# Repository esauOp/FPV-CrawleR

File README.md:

This is a little toy hack. I add an electronics H bridge for speed control and RC compatibility (PWM read).

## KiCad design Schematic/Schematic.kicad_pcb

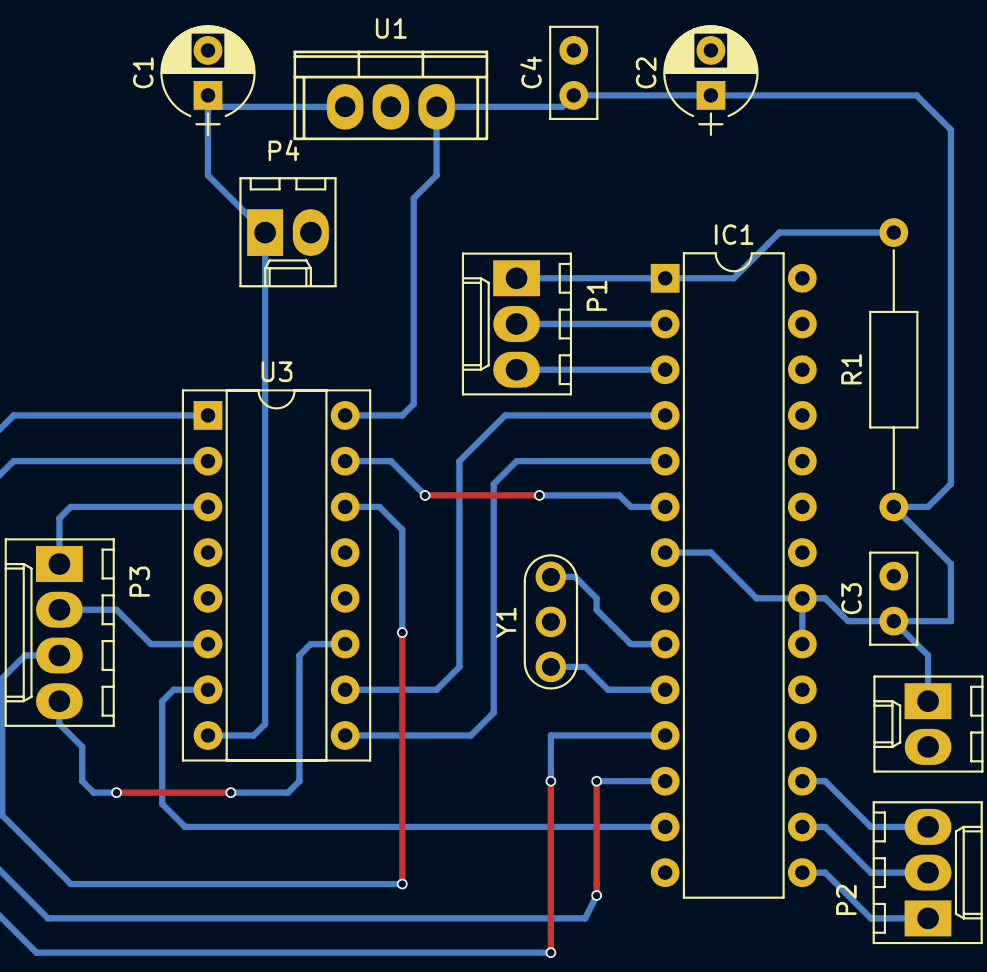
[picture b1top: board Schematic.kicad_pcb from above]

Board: 2 copper layers, 14 parts (0 on the bottom side), 21 nets.

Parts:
C1, C2: 10uF; CP_Radial_D5.0mm_P2.50mm
C3, C4: 100nF; C_Disc_D5.0mm_W2.5mm_P2.50mm
IC1: ATMEGA328-P; DIP-28_W7.62mm
P1: Arduino Programmer; Molex_KK-6410-03_03x2.54mm_Straight
P2: X8R; Molex_KK-6410-03_03x2.54mm_Straight
P3: Motors; Molex_KK-6410-04_04x2.54mm_Straight
P4: Motors Voltage; Molex_KK-6410-02_02x2.54mm_Straight
P5: Rx PS; Molex_KK-6410-02_02x2.54mm_Straight
R1: 10k; R_Axial_DIN0207_L6.3mm_D2.5mm_P15.24mm_Horizontal
U1: LM7805; TO-220
U3: SN754410; DIP-16_W7.62mm_Socket
Y1: Resonator; Resonator-3pin_w7.0mm_h2.5mm

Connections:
+5V: C2.1, C3.1, C4.1, IC1.7, IC1.20, IC1.21, P5.1, R1.1, U1.3, U3.16
+9V: C1.1, P4.1, U1.1, U3.8
GND: C1.2, C2.2, C3.2, C4.2, IC1.8, IC1.22, P4.2, P5.2, U1.2, U3.4, U3.5, U3.12, U3.13, Y1.2
RTS: IC1.1, P1.1, R1.2
Rx: IC1.2, P1.2
Tx: IC1.3, P1.3
ch1: IC1.17, P2.3
ch2: IC1.15, P2.1
ch3: IC1.16, P2.2
m1_a: IC1.4, U3.10
m1_b: IC1.6, U3.15
m1_pwm: IC1.5, U3.9
m2_a: IC1.13, U3.7
m2_b: IC1.12, U3.2
m2_pwm: IC1.11, U3.1
motor1_x: P3.1, U3.3
motor1_y: P3.2, U3.6
motor2_x: P3.3, U3.14
motor2_y: P3.4, U3.11
xt1: IC1.10, Y1.1
xt2: IC1.9, Y1.3

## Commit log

2017-02-11 Iinitial commit.
2017-03-05 Kicad schematic
2017-03-05 Brief readme
2017-03-08 Rx power pins
2017-03-08 ignoring kicad temporary file
